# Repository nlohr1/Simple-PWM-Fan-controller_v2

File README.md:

# Simple-PWM-Fan-controller_v2
Temperature controlled, PWM-steered Voltage-Fan with small Temperature-Range
  
**New Circuit using only few cheap parts: 1 CMOS-Schmitt-Trigger, 2 Diodes, 2 Resistors, a 100k-NTC and a Timing-Capacitor**.

The first version of this Fan-controller had a problem with the NTC-bandwidth (too few resistance-variation, varying temperatures between small bandwidth (here 25°C to 35°C), resulting to output too small and ineffective PWM percentage-variations (about 50% to 60%) to get really usable wide Fan RpM-variations.  
So to get a PWM-variation from 50% to 100% within the targeted small Temperature-Bandwidth Input (10°C difference) it needs a few circuit-modifications.

General Comments
----------------
Many (cheap) fans used for cooling electronic circuits are quite noisy, working at its nominal voltage (mostly 12V), but get quietly reducing its Supply-Voltage. Most of them can start-up and work with down to half of its normal Supply-Voltage. So generally there is no need to operate the fan the whole time with full voltage. "Full-Power" only is needed to cool down peak-temperatures – which may be done with a temperature-dependent variable voltage, using either PWM (Pulse Width Modulation of a DC-Voltage), passing (positive) Voltage-Pulses with variable time-width to the fan-motor or using modern DC-DC-Voltage converters, discarding here old analog converters, which only eliminates upper voltages into heat.  

One disadvantage of a simple PWM-Rectangle-Voltage is - it produces hearable resonances in motor-windings, thus producing more noise as before - if not choosing lower or higher frequency-ranges, which may be either below 30Hz or above 20kHz (resp. non-hearable frequencies...).  
A second disadvantage: PWM-pulses at high frequencies can produce electromagntic disturbances in combination with motor windings (EMC).  
But great advantages of PWM are its simplicity to obtain lower voltages from higher DC-Voltages - together with its heat-preventing principle. So I choosed this principle to generate adaptable voltages, here as a temperature controlled voltage to operate cooling-fans.

As Temperature-Sensor I used a NTC-3950 Thermistor with 100kOhm (at 25°C), which often is used as Temperature-Sensor in 3D-Printers.

The used TC4S-584F IC is a single CMOS Schmitt-Trigger in a small SOT23-5 Package, supporting voltages up to 18V, although it only provides about 4mA maximum Output-Power (in contrast to newer SN74-chips which mostly are faster and "stronger", but can't be run above 5.5V Supply-Voltage) to steer Power-Mosfets.  
This Schmitt-Trigger produces the needed PWM-frequencies in combination with resistor R3 and capacitor C3, modified with resistors R1 and R2. PWM-frequencies vary with temperature, ranging from about 30Hz at Room-Temperature (25°C) to 0Hz (=full-DC-Power) at ~35°C and above. The low PWM-frequency-bandwidth in combination with half-fan-speed results as relatively quiet to noiseless. Nevertheless frequencies can be modified also independently only with time-capacitor C3.

With a small Power-Mosfet in SOT23 package (P-Mosfet IRLML6402 with 20V, 4A, 65mOhm) the PWM-pulses in this frequency-range are steep enough, so heat-losses on this small output stage are negligible.

For greater fans with more Power-consumption (consuming more than about 2 Amps) I suggest to add a N-Mosfet-Stage -as outlined in the schematic- with 1kOhm Gate-Resistor to GND, f.ex. the IRLR2905 with DPAK-Package (55V, **42A**, 27mR and 48nC Gate-Charge).

New circuit Files for DIY-purpose:
----------------------------------
- Schematic and Board files are layouted with Eagle v7.2 Layout-Program,  
- The .png file contains both layout-files as grafical preview: schematic and layout,  
- BOM = Bill o Materials (in html-format) 
- .xln and .dri files contain the drill points for the Board in Excellon-33mm format  
- .nc = gcode drill-file, used to CNC-drill the board out of a blank 2-layer 1,5mm-35my-Cu-Epoxi-Board with ø0,6mm drill,  
   cutting outlines (manually) with about +2mm space to the board-dimension-edges, f.ex. with a fine Proxxon diamond-blade (ø50mm).  
- **TonerDirect:** .pdf file (DIN-A4) for DIY-Board-etching, to transfer both layers per Toner-Transfer-Paper to the drilled (blank) board:  
   using the 4 edge-drills to align the transfer-paper over the predrilled board with 4x ø0,5mm needles / 0,5mm-Cu-wire + adhesive-tape,
   transferring the layout with a modified Laminator @ ~180-200°C with 3 passes to the board. (="Direct Toner-Transfer" method),
   then etching the board with Sodium Persulfate @ ~80°C (5 minutes, if shaking and lifting the board steadily).
   Now straighten edges with the diamond-blade to dimension-outlines. Finally tinning both sides with Solder-paste + flat 80W-soldering-iron
   @ ~360°C + Copper-braid, and insert short strings (~3mm) of head-bent ø0,5mm-Cu-wire in vias, as shown in fotos.

Function of the circuit:
------------------------
Target: At 25°C (room-temperature) the fan shall rotate with 50% PWM-width, increasing with higher ambient-temperature and going up to 100% PWM (=DC) at 35°C +above.

Problem:
--------
Normal NTC-Thermistors are not changing their resistance enough within a small temperature-range (as postulated above with only 10°C difference) to reach a bandwidth changing from 50% PWM-width to 100% (=DC), although the lookup-table of a 100k NTC-3950-Thermistor shows the variation of its resistance in this temperature-range varying from about 100kOhm to 65kOhm, so -at a first glance- this seems to be near enough to the desired PWM-range...

On the other side PWM-circuits with a "Two-Path" Schmitt-Trigger-Feedback uses mostly the Negative-Feedback Line from ST-Output to process the Input, divided with 2 Diodes and going through 2 Resistors, to create the desired two different (+-)PWM-Pulses of a full PWM-Wave. So we have TWO resistors, and each is forming ONE of the two PWM Rectangle-Pulses (+ OR -). So the NTC-Resistor is determining the time-length of ONLY ONE Pulse-rectangle of the PWM-Wave. Our resulting PWM-percentage therefore is determined by the relation of the NTC-resistor to THE SUM OF BOTH  (X per/cent).  
For example if we have 25°C ambient-temperature and the NTC therefore has 100k resistance to form the upper Time-Rectangle, this upper PWM-time should be 50% of one complete PWM-Wave length. Therefore we need the same Resistor-Value (=100k) for the lower PWM-Pulse to get the desired 50% PWM-time. Now the sum of both resitors is 200k.

Calculation of Pulse-Width Percentage (presumed NTC-temperature at 25°C):
-------------------------------------

(100k / 200k) * 100% = 50%.

If the (ambient-)temperature changes to 35°C, the NTC-resistance changes from 100k to 65k, and the sum of both (upper and lower Resistor) = 165k, so the PWM-percentage results as:

(65k / 165k) * 100% = 40%  (=shorter than before?)

Yes, shorter! Because its only the calculated "lower" 40%-Pulse-Width/length on the ST-INPUT. The ST inverts this pulse on his OUTPUT, with same time-length, but as a HIGH Output-"Off"-Pulse (on P-Mosfet Q1), so for the "On"-part of the PWM we have to take the complementary LOW (Gate)-"On-Time"-length of the ST-Output - which appears at same time as HIGH-Output on the Mosfet-Stage-Output, this beeing the "active", width- or length-changing part of our measured, increasing NTC-Temperature (=decreasing NTC-Resistance!). So to calculate this length we substract resulted 40% from the total of 100%-Pulse-width, getting the 60% "active" (high)-Pulse-time-length, provided to the fan.  
So the new (+)Pulse-Width has changed from 50% to 60% of total length. But this is only a small change of 10% of the complete (100%) PWM-Wave-time (length), but not the desired change from 50% to 100% PWM (to make continuous +DC-Voltage out of the initial 25°C / 50%-Pulse-Width)!

This "percentage"-problem also persists in other circuit-principles, because most Schmitt-Triggers have fixed built-in hysteresis-levels, mostly at *about* 1/3 and 2/3 of their Supply-Voltage. So also the often used "good old" NE555 (also beeing a "Schmitt-Trigger"!). But on the other hand no NTC can change from "100%" to "0" (to that within a small temperature-range as targeted) - to get a 50% to 100% PWM-bandwidth on a simple ST-Output...

But how do we solve this problem - getting out a 50% PWM ***VARIATION*** having only a small Temperature-Range on the Sensor?

Considered Solutions:
---------------------
1. increasing/transducing the NTC-Voltage-"Bandwidth" - f.ex. with an additional OP-Amplifier,  
2. using an OPAmp to design a Schmitt-Trigger with smaller hysteresis-limits as the common fixed ones,  
3. decreasing (fixed) Hysteresis of a generic Schmitt-Tigger - f.ex. with Resistors *),  
4. using a commercial IC, made to steer fans with a temperature-dependent PWM (f.ex. the TC648),  
5. using a uController, "mapping"(=calculating) measured NTC-voltages to defined (greater) PWM-output ranges,  
6. using other Temperature-Sensors...

*) I choosed the third way because of its simplicity, as demonstrated in the schematic, using a simple CMOS Schmitt-Trigger in conjunction with the inverting stage of the Output-Mosfet, used as "positive-feedback booster", this generating opposite signals to the ST-Output, which (virtually) decreases the original hysteresis-bandwidth.  
This "POSITIVE-feedback" Signal-Path now contains the NTC and the compensating "50%-low" timing-resistor - in opposite to the normally used NEGATIVE-feedback-path from ST, containing the two timing-resistors.
So both, R1 and R2, now used as positive-feedback-resistors, are acting in opposite direction to the ST-Output-Signal, this created in conjunction with R3, the "pilot"-timing-resistor and capacitor C3, so R1 and R2 are forming **two Voltage-Dividers** in conjunction with R3, one for each Pulse-direction.  
Both Voltage-Dividers are "adding" their opposite, substracting-current to the ST's Output-current (on R3), so the resulting new (virtual) threshold-levels are nearer together as the original fixed ones, getting (virtually) decreased hysteresis-limits.

**The trick hereby is the Voltage-Divider** between NTC R1 and the leading timing-resistor R3. R3 subtracts / eliminates the unneeded (virtually "persistent" or "inactive") part of NTCs total Resistance-Value, while the resting small "active", temperature-changing part of this NTC appears on the ST's Input as a WHOLE (voltage-) RANGE between "0" and "100", so the (fixed) ST-hysteresis traduces this range in corresponding PWM-time-percentages of 50% to 100%, this now beeing proportional to the given small input-temperature-range!  

Function:
---------
If the NTC is warming up, its resistance lessens down, so (through Diode D1) it pulls the middle of its Voltage-Divider R1/R3 with attached capacitor C3 high, but on the other side R3 pulls C3 a bit more down as NTC R1, because of its "stronger" (lower) resistance-value, so the resulting voltage on C3 anyhow goes slowly down, till reaching the lower ST-threshold-line. This threshold abruptly changes the status of the ST-OUTPUT from low to high and the Mosfet-Inverter (the Power-Stage) from high to low. So now the second Voltage-Divider with R2 and R3 becomes active (through Diode D2) - while Diode D1 is blocking this direction, so NTC is inactive: C3 is pulled slowly high till reaching the upper ST-threshold-level. There again both Outputs change their Status and the process begins from start, as described.  
So both directions are forming their own Output-Pulse length and Puls direction. The lenghts are formed with the time-difference resulting from each initial Voltage-Divider-LEVELs (=after each direction-change) in conjunction with C3 going slowly to its opposite ST-threshold-level.  
But in case that the NTC becomes hotter than 35°C, its Voltage-Divider-point (R1/R3) can't pull C3 anymore sufficiently down to the lower threshold-line, remainig above this line, so no Output changes: The ST-Output remains on "Zero" (DC-Voltage), the Mosfet-Output stays at +VCC and so the fan at "full-power" (as desird).  

Changing the (default) PWM-Frequency-Range with C3:
---------------------------------------------------
Of course PWM-Frequencies of this circuit, with two ADDED resistances (R1 and R2) substracting current to R3, are resulting in lower frequencies as without Volage-Divider, with only one resistor (R3) as leading time-resistor.  
But if needed, the resulting (default) "25°C"-Frequency may be adjusted, changing only the value of timing-capacitor C3. With higher C3-capacity, frequency goes lower and viceversa.  
I choosed a low 40-to-0Hz-range, because high PWM-frequency ranges (above 20kHz and more) may cause severe EMV-Problems in conjunction with motor-windings...

Changing the Temperature-Range:
-------------------------------
If the **temperature**-range (here choosen between 25°C and 35°C) results as too small, the virtually "persistent" resistance-part of our NTC may be increased, so f.ex. adding a 10k-resistor (as outlined, here R5 in schematics)...  
**But Warning**: the resulting Signal-Amplification of this circuit is relatively high (as calculated above), so values for R3, together with R2 and  
NTC R1 + the 2 direction-Diodes (with its 0,7V threshold voltage) are relatively critical, considering ST's threshold-lines in correlation to our 
two R-Dividers "virtual thresholds" (mid-point voltages) on C3. If one of both ST-thresholds are not reached anymore, PWM is going down to either 0V or VCC.

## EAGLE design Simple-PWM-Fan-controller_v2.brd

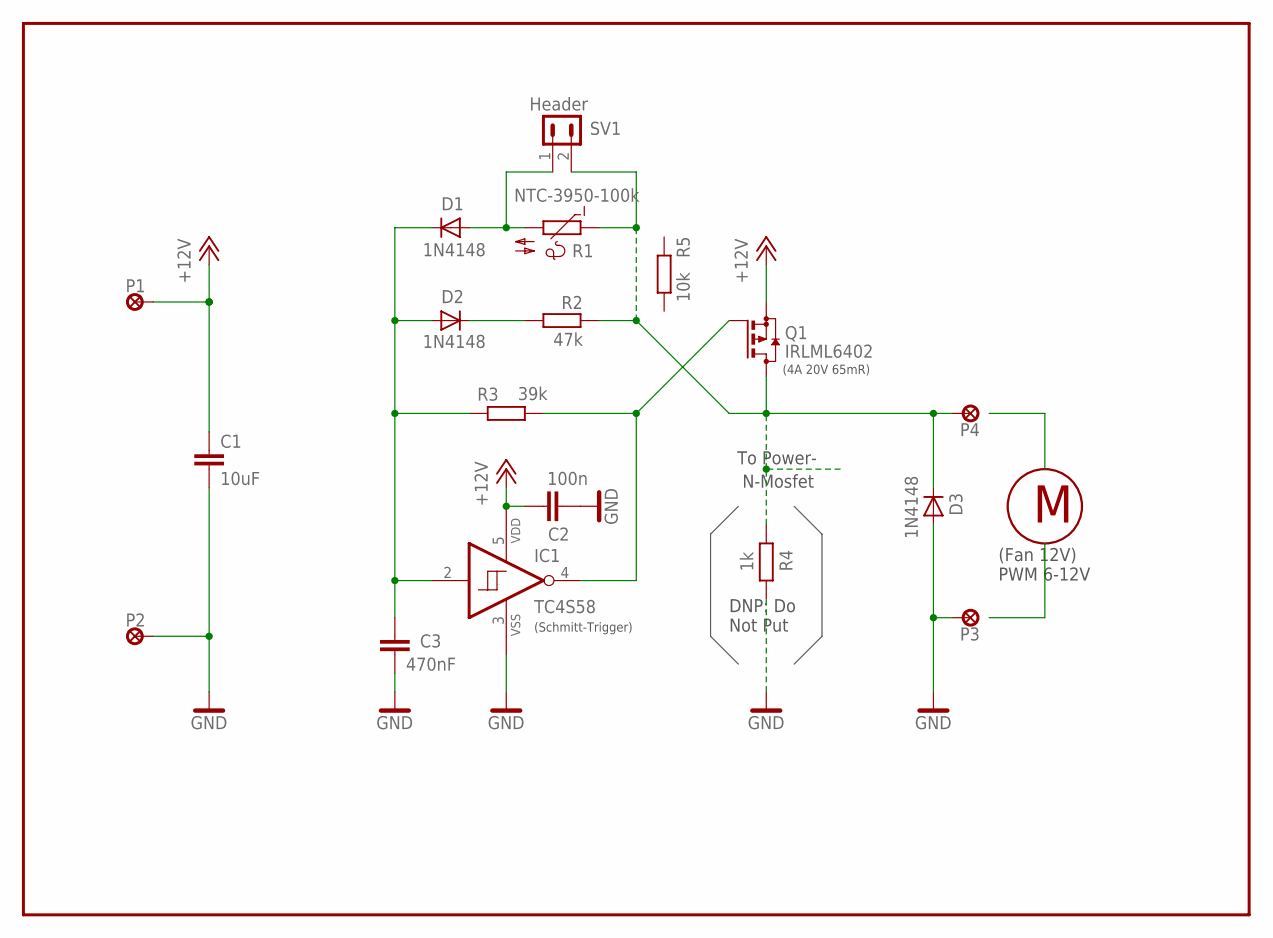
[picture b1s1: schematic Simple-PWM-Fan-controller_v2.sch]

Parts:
C1: 10uF; C1206
C2: 100n; C0603
C3: 470nF; C0603
D1, D2, D3: 1N4148; SOD323-R
IC1: TC4S58; SSOP5P09
P1, P2, P3, P4: LSP17
Q1: IRLML6402; SOT23
R1: NTC-3950-100k; P640
R2: 47k; R0603
R3: 39k; R0603
R4: 1k; R0805
R5: 10k; R0603
SV1: Header; MA02-1R

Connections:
+12V: C1.1, C2.1, IC1.5 (VDD), P1.P$1, Q1.2 (S)
GND: C1.2, C2.2, C3.2, D3.A, IC1.3 (VSS), P2.P$1, P3.P$1, R4.1
unnamed: C3.1, D1.C, D2.A, IC1.2 (I), R3.1
unnamed: D1.A, R1.2, SV1.1
unnamed: D3.C, P4.P$1, Q1.3 (D), R1.1, R2.2, R4.2, SV1.2
unnamed: D2.C, R2.1
unnamed: IC1.4 (O), Q1.1 (G), R3.2

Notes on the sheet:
(Fan 12V) PWM 6-12V
(4A 20V 65mR)
(Schmitt-Trigger)
DNP: Do Not Put
To Power- N-Mosfet

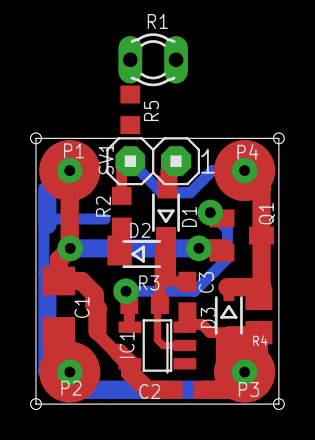
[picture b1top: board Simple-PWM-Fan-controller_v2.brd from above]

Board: 2 copper layers, 13.5 x 14.8 mm, 18 parts (0 on the bottom side), 7 nets.
